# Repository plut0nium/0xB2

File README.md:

# 0xB2 - splinky
Pro-Micro/Elite-C replacement with USB-C and RP2040.

Designed for use in custom mechanical (split) keyboards, but many other uses are possible.

## Features:

 * Pro-micro / Sparkfun RP2040 compatible footprint, with 5 extra pins at bottom (Elite-C style)
 * Raspberry Pi RP2040 MCU
 * Up to 16MB flash memory _(depending on component selection and availability)_
 * User LED & USB VBUS detect
 * Low profile USB-C mid-mount connector
 * Designed to be manufactured and assembled by all common PCBA services (including JLCPCB)

<!---->

## Pinout

The pinout is compatible with the widely available [SparkFun RP2040](https://www.sparkfun.com/products/18288), with extra GPIO12..16 pins broken out on the lower side.

USB VBUS detection on GPIO19.

> This pinout is a _de facto_ standard, established by actors of the MK community (see discussions in `#RP2040` on the bastardkb Discord server) 

Additionnaly, a user LED is tied to GPIO17, can be used for UF2 bootloader status indication, or any other purpose (or turned OFF, no annoying always-on power LED).

diagram with qmk rp2040 naming, avr and arduino mapping below

## Programming

The splinky uses a basic two-button reset circuitry.

In order to put the board in bootloader mode, press briefly the RESET button (marked **R**) while holding the BOOT button (the second one).
If the buttons are not reachable (soldered upside down), the /RST pad can be shorted to GND, while the two smaller BOOT pads (next to D8) are maintained shorted (v2 only).

## Manufacturing

Releases contain required information (gerbers, bom, pos) for assembly by JLCPCB.

## Releases

 * **v3** updated pinout - current release
 * **v2** first public release
 * **v1** first prototyping run

## Credits

 * Raspberry Pi Foundation
   * [RP2040 Datasheet](https://datasheets.raspberrypi.com/rp2040/rp2040-datasheet.pdf)
   * [Hardware design with RP2040](https://datasheets.raspberrypi.com/rp2040/hardware-design-with-rp2040.pdf)
 * [SparkFun Pro Micro - RP2040](https://www.sparkfun.com/products/18288)
 * [Adafruit kb2040](https://learn.adafruit.com/adafruit-kb2040)
 * [sea-picro](https://github.com/joshajohnson/sea-picro) - _similar project, I borrowed some cheaper component references ^^_
 * ...

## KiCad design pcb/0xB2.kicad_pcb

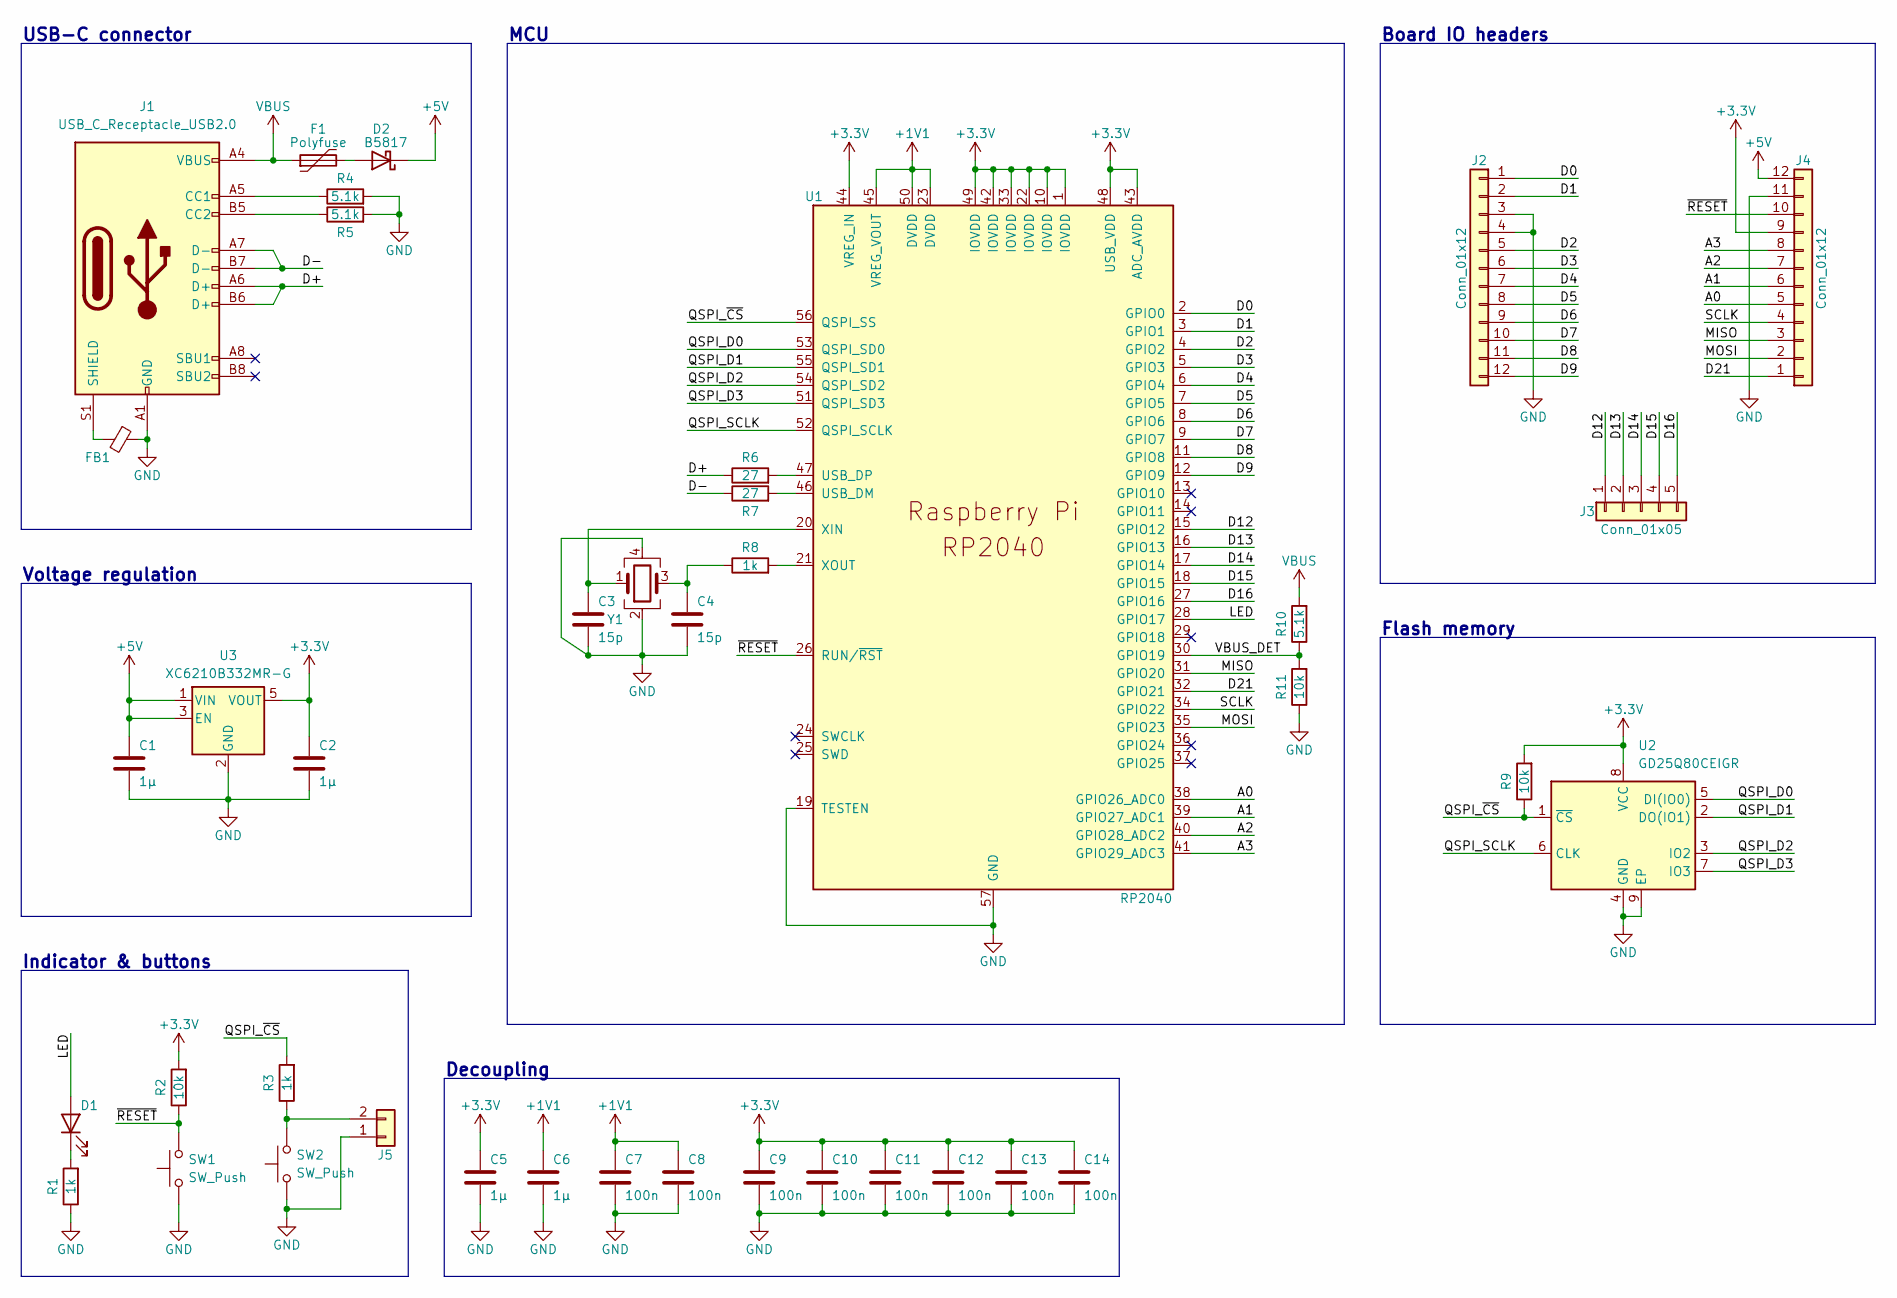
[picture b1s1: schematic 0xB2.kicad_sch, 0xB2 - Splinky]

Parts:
C1, C2: 1µ; C_0603_1608Metric; LCSC C19666
C3, C4: 15p; C_0402_1005Metric; LCSC C1548
C5, C6: 1µ; C_0402_1005Metric; LCSC C52923
C7, C8, C9, C10, C11, C12, C13, C14: 100n; C_0402_1005Metric; LCSC C1525
D1: LED; LED_0402_1005Metric; LCSC C130719
D2: B5817; D_SOD-323; LCSC C123899
F1: Polyfuse; Fuse_0603_1608Metric; LCSC C69679
FB1: FerriteBead_Small; L_0603_1608Metric; LCSC C98288
J1: USB_C_Receptacle_USB2.0; USB_C_Receptacle_HRO_TYPE-C-31-M-13B; LCSC C2848619
J2, J4: Conn_01x12; PinHeader_1x12_P2.54mm
J3: Conn_01x05; PinHeader_1x05_P2.54mm
J5: Conn_01x02; PinHeader_1x02_P1.27mm_Vertical
R1, R3, R8: 1k; R_0402_1005Metric; LCSC C11702
R2, R9, R11: 10k; R_0402_1005Metric; LCSC C25744
R4, R5, R10: 5.1k; R_0402_1005Metric; LCSC C25905
R6, R7: 27; R_0402_1005Metric; LCSC C25100
SW1, SW2: SW_Push; SW_SPST_CK_KXT3; LCSC C319433
U1: RP2040; QFN-56-1EP_7x7mm_P0.4mm_EP3.2x3.2mm; LCSC C2040
U2: GD25Q80CEIGR; USON-8-1EP_3x2mm_P0.5mm_EP0.25x1.65mm; LCSC C395484
U3: XC6210B332MR-G; SOT-23-5; LCSC C82942
Y1: Crystal_GND24; Crystal_SMD_2520-4Pin_2.5x2.0mm; LCSC C2149204

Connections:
+1V1: C6.1, C7.1, C8.1, U1.23 (DVDD), U1.45 (VREG_VOUT), U1.50 (DVDD)
+3V3: C2.1, C5.1, C9.1, C10.1, C11.1, C12.1, C13.1, C14.1, J4.9, R2.2, R9.2, U1.1 (IOVDD), U1.10 (IOVDD), U1.22 (IOVDD), U1.33 (IOVDD), U1.42 (IOVDD), U1.43 (ADC_AVDD), U1.44 (VREG_IN), U1.48 (USB_VDD), U1.49 (IOVDD), U2.8 (VCC), U3.5 (VOUT)
+5V: C1.1, D2.1 (K), J4.12, U3.1 (VIN), U3.3 (EN)
/A0: J4.5, U1.38 (GPIO26_ADC0)
/A1: J4.6, U1.39 (GPIO27_ADC1)
/A2: J4.7, U1.40 (GPIO28_ADC2)
/A3: J4.8, U1.41 (GPIO29_ADC3)
/D0: J2.1, U1.2 (GPIO0)
/D1: J2.2, U1.3 (GPIO1)
/D2: J2.5, U1.4 (GPIO2)
/D3: J2.6, U1.5 (GPIO3)
/D4: J2.7, U1.6 (GPIO4)
/D5: J2.8, U1.7 (GPIO5)
/D6: J2.9, U1.8 (GPIO6)
/D7: J2.10, U1.9 (GPIO7)
/D8: J2.11, U1.11 (GPIO8)
/D9: J2.12, U1.12 (GPIO9)
/D12: J3.1, U1.15 (GPIO12)
/D13: J3.2, U1.16 (GPIO13)
/D14: J3.3, U1.17 (GPIO14)
/D15: J3.4, U1.18 (GPIO15)
/D16: J3.5, U1.27 (GPIO16)
/D21: J4.1, U1.32 (GPIO21)
/D+: J1.A6 (D+), J1.B6 (D+), R6.1
/D-: J1.A7 (D-), J1.B7 (D-), R7.1
/LED: D1.2 (A), U1.28 (GPIO17)
/MISO: J4.3, U1.31 (GPIO20)
/MOSI: J4.2, U1.35 (GPIO23)
/QSPI_D0: U1.53 (QSPI_SD0), U2.5 (DI(IO0))
/QSPI_D1: U1.55 (QSPI_SD1), U2.2 (DO(IO1))
/QSPI_D2: U1.54 (QSPI_SD2), U2.3 (IO2)
/QSPI_D3: U1.51 (QSPI_SD3), U2.7 (IO3)
/QSPI_SCLK: U1.52 (QSPI_SCLK), U2.6 (CLK)
/QSPI_~CS: R3.2, R9.1, U1.56 (QSPI_SS), U2.1 (~CS)
/SCLK: J4.4, U1.34 (GPIO22)
/VBUS_DET: R10.1, R11.2, U1.30 (GPIO19)
/~RESET: J4.10, R2.1, SW1.2, U1.26 (RUN/~RST)
GND: C1.2, C2.2, C3.2, C4.2, C5.2, C6.2, C7.2, C8.2, C9.2, C10.2, C11.2, C12.2, C13.2, C14.2, FB1.1, J1.A1 (GND), J1.A12 (GND), J1.B1 (GND), J1.B12 (GND), J2.3, J2.4, J4.11, J5.1, R1.1, R4.2, R5.2, R11.1, SW1.1, SW2.1, U1.19 (TESTEN), U1.57 (GND), U2.4 (GND), U2.9 (EP), U3.2 (GND), Y1.2, Y1.4
unnamed: C3.1, U1.20 (XIN), Y1.1
unnamed: C4.1, R8.1, Y1.3
unnamed: D1.1 (K), R1.2
unnamed: D2.2 (A), F1.2
unnamed: FB1.2, J1.S1 (SHIELD)
unnamed: J1.A5 (CC1), R4.1
unnamed: J1.B5 (CC2), R5.1
unnamed: J5.2, R3.1, SW2.2
unnamed: R6.2, U1.47 (USB_DP)
unnamed: R7.2, U1.46 (USB_DM)
unnamed: R8.2, U1.21 (XOUT)
VBUS: F1.1, J1.A4 (VBUS), J1.A9 (VBUS), J1.B4 (VBUS), J1.B9 (VBUS), R10.2

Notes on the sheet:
Decoupling
Board IO headers
USB-C connector
Indicator & buttons
Voltage regulation
MCU
Flash memory

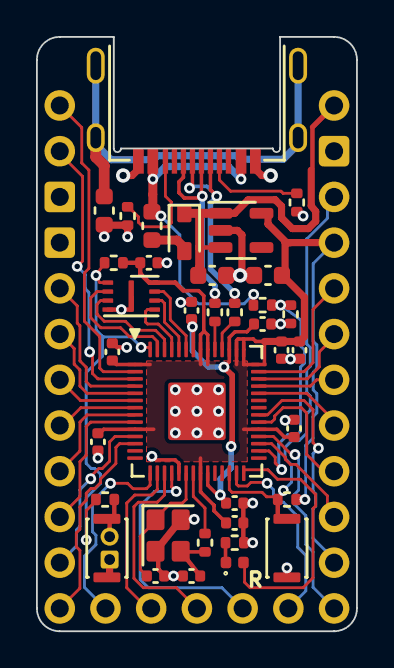
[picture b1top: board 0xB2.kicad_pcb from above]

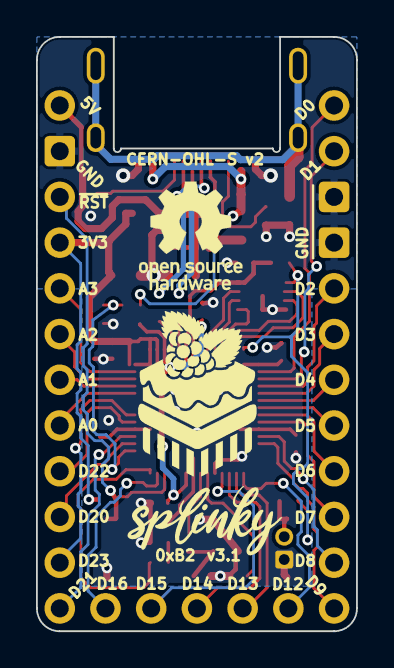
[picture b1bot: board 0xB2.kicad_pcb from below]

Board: 2 copper layers, 17.8 x 33.0 mm, 42 parts (2 on the bottom side), 50 nets.

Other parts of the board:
rb_cake: G*****; rb_cake
splinky: G*****; splinky

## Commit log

2022-03-13 Add LICENCE - CERN-OHL-S
2022-03-13 Add README
2022-03-13 PCB data
2022-03-13 Minor routing corrections
2022-03-13 Add silkscreen drawing
2022-03-14 Smaller crystal footprint > 2520
2022-03-14 Add BOOT pad on bottom layer
2022-03-14 New ref for D2
2022-03-14 Silkscreen update
2022-03-14 README update - rename to splinky
2022-03-17 Add USB VBUS detect on GPIO 25
2022-03-17 Prepare BOM & POS for pre-release
2022-04-20 Break out 5V instead of VBUS + routing update
2022-04-20 Make the pinout compatible with KB2040
    WARNING !!! Breaks the compatibility with v1
2022-04-21 Minor routing changes
2022-04-21 Change to Sparkfun RP2040 pinout
2022-04-22 Add pins for BOOT from the back
2022-04-22 README and doc update
2022-04-24 silkscreen correction
2022-04-24 README update
2022-04-24 add picture
2022-04-27 Get v2 ready for manufacturing
2022-06-14 Update pinout
    Use of the agreed pinout (see discussions on bkb discord)
    for bottom row and VBUS detect.
    Maintain compatibility with Sparkfun RP2040.
2022-06-14 Update doc for v3
2022-06-15 update JLC part to usb c M13
2022-06-15 switch to M13
2022-06-15 edge cuts
2022-06-15 routing
2022-06-15 silkscreen
2022-06-15 Switch USB-C connector
2023-08-06 Update README.md to add the pinout mapping

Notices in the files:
pcb/0xB2.kicad_pcb:
CERN-OHL-S v2
